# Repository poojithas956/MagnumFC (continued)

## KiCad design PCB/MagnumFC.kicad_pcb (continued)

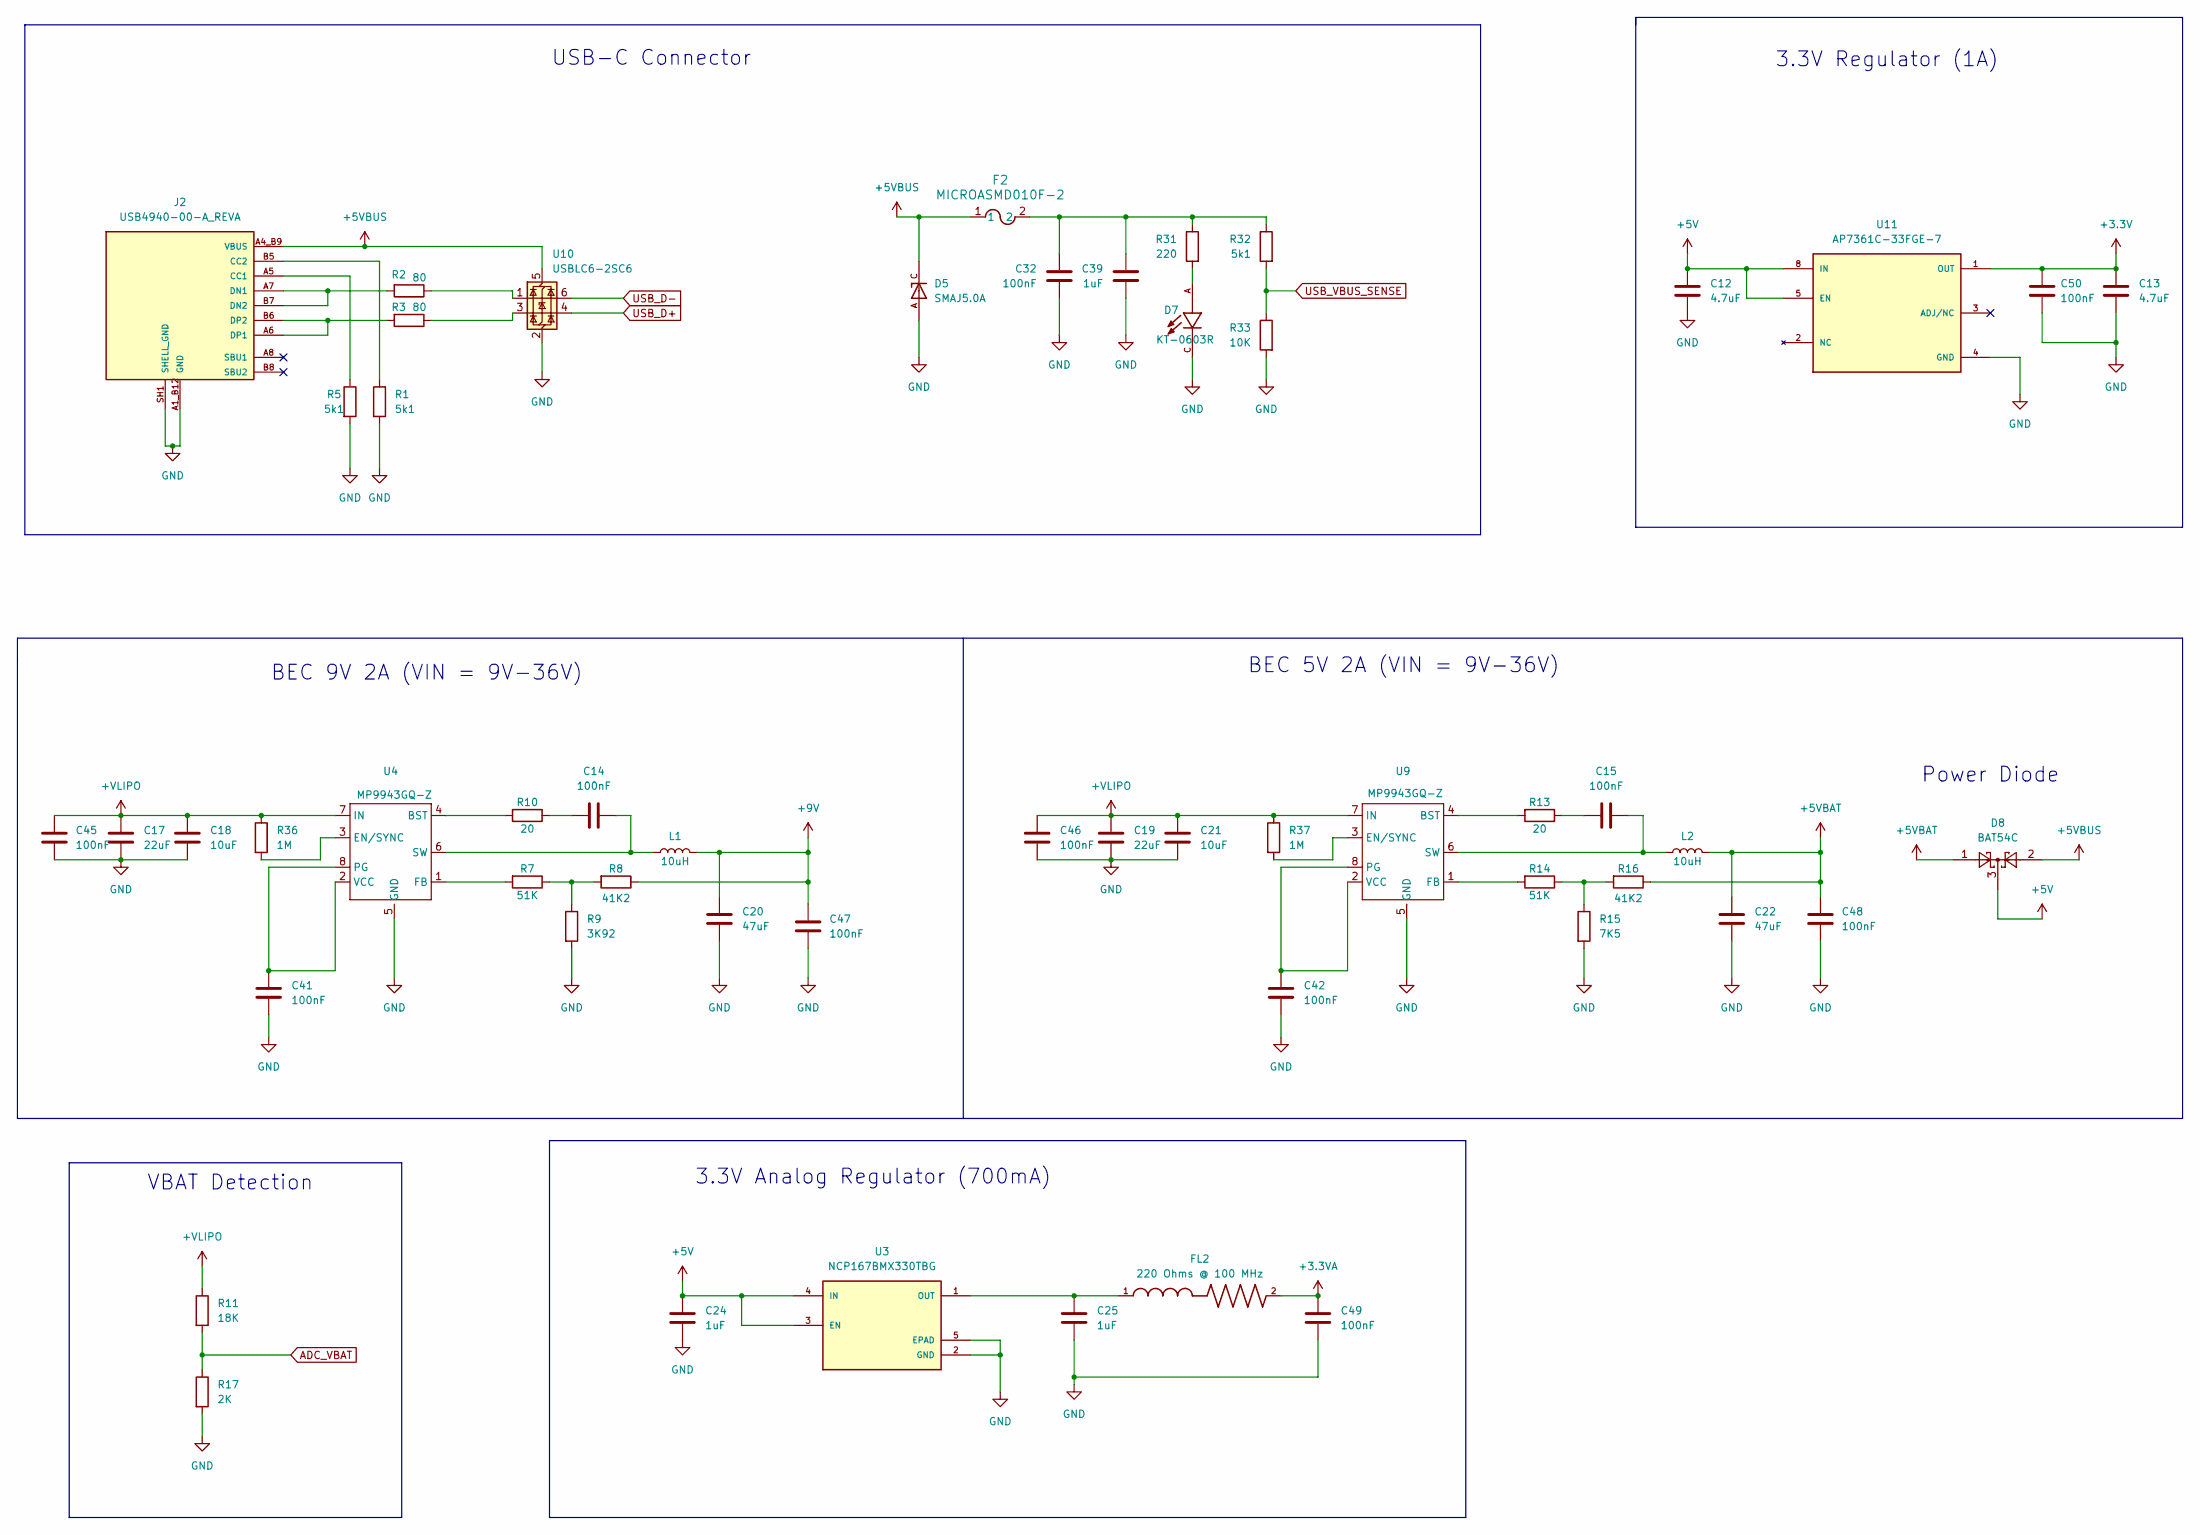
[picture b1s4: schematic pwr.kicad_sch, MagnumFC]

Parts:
C12, C13: 4.7uF; C_0603_1608Metric; MANUFACTURER PART NUMBER CL10A475KO8NNNC; LCSC C19666
C14, C15, C32, C41, C42, C45, C46, C47, C48, C49, C50: 100nF; C_0402_1005Metric; MANUFACTURER PART NUMBER CL05A104KA5NNNC; LCSC C100072
C17, C19: 22uF; C_0805_2012Metric; MANUFACTURER PART NUMBER HGC0805R5226M350NSLJ; LCSC C22367832
C18, C21: 10uF; C_0805_2012Metric; MANUFACTURER PART NUMBER CL21A106KBYQNNE; LCSC C2932476
C20, C22: 47uF; C_0805_2012Metric; MANUFACTURER PART NUMBER CL21A476MPYNNWE; LCSC C5596752
C24, C25, C39: 1uF; C_0402_1005Metric; MANUFACTURER PART NUMBER CL05A105KO5NNNC; LCSC C29266
D5: SMAJ5.0A; DIOM4325X250N; PARTREV S2102; LCSC C83329
D7: KT-0603R; LED_KT-0603R; PARTREV 2013/01/24; LCSC C2286
D8: BAT54C; SOT-23; MANUFACTURER PART NUMBER BAT54CLT1G; LCSC C14308
F2: MICROASMD010F-2; FUSE_MICROASMD010F_LTF; MANUFACTURER PART NUMBER MICROSMD010F-2; LCSC C2649903
FL2: 220 Ohms @ 100 MHz; L_0402_1005Metric; MANUFACTURER PART NUMBER BLM15BB221SN1D; LCSC C85818
J2: USB4940-00-A_REVA; GCT_USB4940-00-A_REVA; PARTREV A; LCSC C54829818
L1, L2: 10uH; L_Changjiang_FTC404020S; MANUFACTURER PART NUMBER GXTC0420-100-MT; LCSC C53198553
R1, R5, R32: 5k1; R_0402_1005Metric; MANUFACTURER PART NUMBER RC0402FR-075K1L; LCSC C105872
R2, R3: 80; R_0402_1005Metric; MANUFACTURER PART NUMBER RC0402FR-0780R6L; LCSC C185392
R7, R14: 51K; R_0402_1005Metric; MANUFACTURER PART NUMBER RC0402FR-0751KL; LCSC C107229
R8, R16: 41K2; R_0402_1005Metric; MANUFACTURER PART NUMBER CRCW040241K2FKED; LCSC C844310
R9: 3K92; R_0402_1005Metric; MANUFACTURER PART NUMBER RC0402FR-073K9L; LCSC C131467
R10, R13: 20; R_0402_1005Metric; MANUFACTURER PART NUMBER RC0402FR-0720RL; LCSC C138031
R11: 18K; R_0402_1005Metric; MANUFACTURER PART NUMBER 0402WGF1802TCE; LCSC C25762
R15: 7K5; R_0402_1005Metric; MANUFACTURER PART NUMBER 0402WGF7501TCE; LCSC C25918
R17: 2K; R_0402_1005Metric; MANUFACTURER PART NUMBER RC0402FR-072KL; LCSC C60488
R31: 220; R_0402_1005Metric; MANUFACTURER PART NUMBER RC0402FR-07220RL; LCSC C112291
R33: 10K; R_0402_1005Metric; MANUFACTURER PART NUMBER RC0402JR-0710KL; LCSC C60489
R36, R37: 1M; R_0402_1005Metric; MANUFACTURER PART NUMBER RC0402JR-071ML; LCSC C93949
U3: NCP167BMX330TBG; VREG_NCP167BMX330TBG; PARTREV 5; LCSC C892227
U4, U9: MP9943GQ-Z; QFN-8_MP9943_MNP; MANUFACTURER PART NUMBER MP9943GQ-Z; LCSC Mouser No: 946-MP9943GQ-Z
U10: USBLC6-2SC6; SOT-23-6; MANUFACTURER PART NUMBER USBLC6-2SC6; LCSC C7519
U11: AP7361C-33FGE-7; SON65P300X300X63-9N; PARTREV 5 - 2; LCSC C151007

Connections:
+3.3V: C13.1, C50.1, U11.1 (OUT); also elsewhere on the board
+3.3VA: C49.1, FL2.2; also elsewhere on the board
+5V: C12.1, C24.1, D8.3, U3.3 (EN), U3.4 (IN), U11.5 (EN), U11.8 (IN); also elsewhere on the board
+5VBAT: C22.1, C48.1, D8.1, L2.2, R16.1
+5VBUS: D5.C, D8.2, F2.1, J2.A4_B9 (VBUS), J2.B4_A9 (VBUS), U10.5 (VBUS)
+9V: C20.1, C47.1, L1.2, R8.1; also elsewhere on the board
+VLIPO: C17.1, C18.1, C19.1, C21.1, C45.1, C46.1, R11.1, R36.1, R37.1, U4.7 (IN), U9.7 (IN); also elsewhere on the board
ADC_VBAT: R11.2, R17.1; also elsewhere on the board
GND: C12.2, C13.2, C17.2, C18.2, C19.2, C20.2, C21.2, C22.2, C24.2, C25.2, C32.2, C39.2, C41.2, C42.2, C45.2, C46.2, C47.2, C48.2, C49.2, C50.2, D5.A, D7.C, J2.A1_B12 (GND), J2.B1_A12 (GND), J2.SH1 (SHELL_GND), J2.SH2 (SHELL_GND), J2.SH3 (SHELL_GND), J2.SH4 (SHELL_GND), R1.2, R5.2, R9.2, R15.2, R17.2, R33.2, U3.2 (GND), U3.5 (EPAD), U4.5 (GND), U9.5 (GND), U10.2 (GND), U11.4 (GND), U11.9 (GND); also elsewhere on the board
unnamed: C14.2, R10.1
unnamed: C15.2, R13.1
unnamed: C32.1, C39.1, F2.2, R31.1, R32.1
unnamed: D7.A, R31.2
unnamed: J2.A5 (CC1), R5.1
unnamed: J2.B5 (CC2), R1.1
unnamed: J2.A7 (DN1), J2.B7 (DN2), R2.2
unnamed: J2.A6 (DP1), J2.B6 (DP2), R3.2
unnamed: R2.1, U10.1 (I/O1)
unnamed: R3.1, U10.3 (I/O2)
unnamed: R7.1, R8.2, R9.1
unnamed: R14.1, R15.1, R16.2
unnamed: C25.1, FL2.1, U3.1 (OUT)
unnamed: R10.2, U4.4 (BST)
unnamed: R36.2, U4.3 (EN/SYNC)
unnamed: R7.2, U4.1 (FB)
unnamed: C41.1, U4.2 (VCC), U4.8 (PG)
unnamed: C14.1, L1.1, U4.6 (SW)
unnamed: R13.2, U9.4 (BST)
unnamed: R37.2, U9.3 (EN/SYNC)
unnamed: R14.2, U9.1 (FB)
unnamed: C42.1, U9.2 (VCC), U9.8 (PG)
unnamed: C15.1, L2.1, U9.6 (SW)
USB_D+: U10.4 (I/O2); also elsewhere on the board
USB_D-: U10.6 (I/O1); also elsewhere on the board
USB_VBUS_SENSE: R32.2, R33.1; also elsewhere on the board

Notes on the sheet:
USB-C Connector
3.3V Analog Regulator (700mA)
VBAT Detection
BEC 5V 2A (VIN = 9V-36V)
BEC 9V 2A (VIN = 9V-36V)
Power Diode
3.3V Regulator (1A)

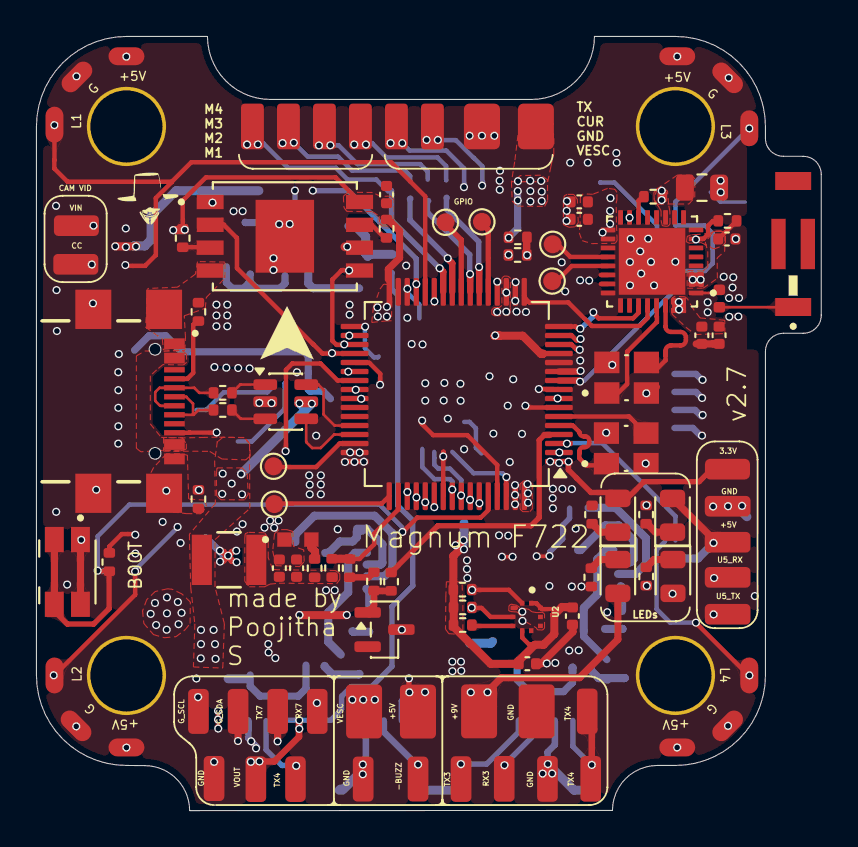
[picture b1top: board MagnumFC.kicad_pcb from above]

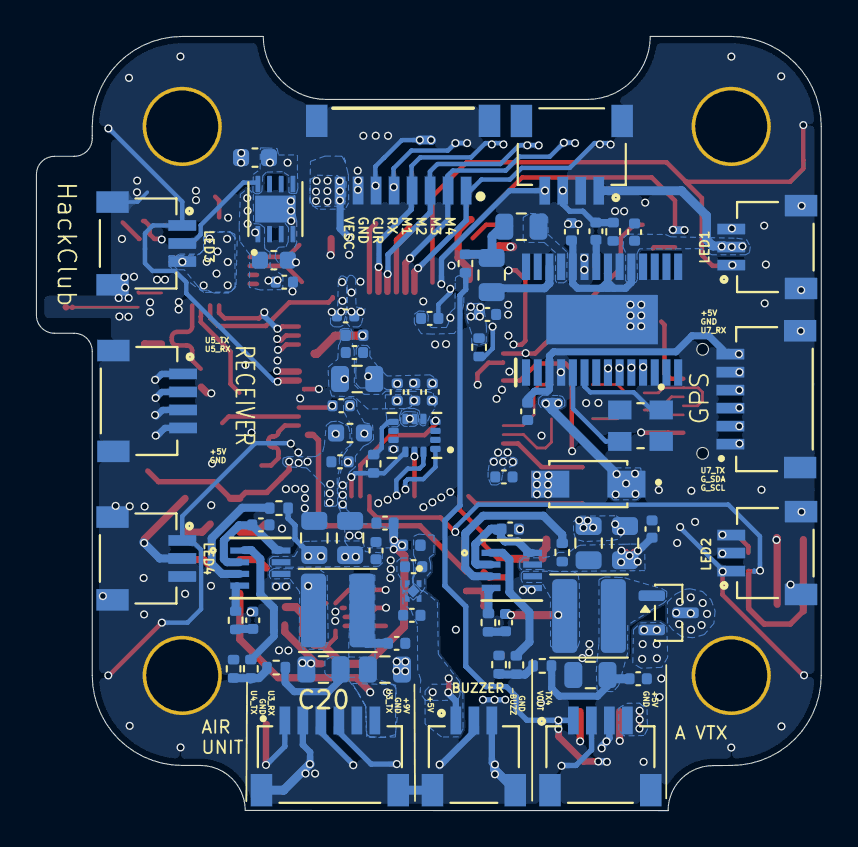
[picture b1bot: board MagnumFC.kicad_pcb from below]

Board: 6 copper layers, 43.6 x 43.0 mm, 180 parts (77 on the bottom side), 107 nets.

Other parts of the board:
TP36#2: TestPoint; TestPoint_Pad_1.0x1.0mm

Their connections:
GND: TP36#2.1 (1_1); also elsewhere on the board

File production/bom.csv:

Designator,Footprint,Quantity,Value,LCSC Part #
"_3, _2, ",,3,,
AT1,ANTENNA_2450AT43B100E,1,2450AT43B100E,C2917721
"C1, C11, C14, C15, C16, C2, C23, C26, C27, C28, C29, C3, C30, C32, C35, C36, C38, C4, C41, C42, C44, C45, C46, C47, C48, C49, C50, C6",0402,28,100nF,C100072
"C10, C33",0402,2,10nF,C15195
"C12, C13, C5",0603,3,4.7uF,C19666
"C17, C19, C31, C40, C43",0805,5,22uF,C22367832
"C18, C21, C37",0805,3,10uF,C2932476
"C20, C22",0805,2,47uF,C5596752
"C24, C25, C34, C39",0402,4,1uF,C29266
C7,0805,1,1uF,C24123
"C8, C9",0402,2,2.2uF,C107369
D1,0805,1,LED2,C2293
D2,0805,1,LED3,C2296
D3,0805,1,LED4,C2297
D4,0805,1,LED1,C2295
D5,DIOM4325X250N,1,SMAJ5.0A,C83329
D7,LED_KT-0603R,1,KT-0603R,C2286
D8,SOT-23,1,BAT54C,C14308
F2,FUSE_MICROASMD010F_LTF,1,MICROASMD010F-2,C2649903
FL1,0402,1,120 Ohms @ 100 MHz,C107331
FL2,0402,1,220 Ohms @ 100 MHz,C85818
IC1,SOP65P640X120-29N,1,AT7456E,C82351
"J1, J9",JST_SM06B-SRSS-TB_LF__SN_,2,SM06B-SRSS-TB_LF__SN_,C2845365
"J10, J13, J14",JST_SM04B-SRSS-TB_LF__SN_,3,SM04B-SRSS-TB_LF__SN_,C2845363
"J12, J3, J5, J7, J8",JST_SM03B-SRSS-TB_LF__SN_,5,SM03B-SRSS-TB_LF__SN_,C2845362
J2,GCT_USB4940-00-A_REVA,1,USB4940-00-A_REVA,C54829818
J6,JST_SM08B-SRSS-TB_LF__SN_,1,SM08B-SRSS-TB_LF__SN_,C160407
"L1, L2",L_Changjiang_FTC404020S,2,10uH,C53198553
L3,0402,1,1.8nH,C77107
Q2,SOT-23,1,AO3400A,C20917
"R1, R32, R5",0402,3,5k1,C105872
"R10, R13",0402,2,20,C138031
R11,0402,1,18K,C25762
"R12, R20, R24, R33, R35, R4, R6",0402,7,10K,C60489
"R14, R7",0402,2,51K,C107229
R15,0402,1,7K5,C25918
"R16, R8",0402,2,41K2,C844310
R17,0402,1,2K,C60488
R18,0402,1,47,C137973
"R2, R3",0402,2,80,C185392
"R21, R31",0402,2,220,C112291
"R22, R34",0402,2,1K,C106235
"R23, R30, R38",0402,3,75,C137841
"R25, R26",0402,2,2.2K,C163447
"R27, R28, R29",0402,3,4.7K,C105871
"R36, R37",0402,2,1M,C93949
R9,0402,1,3K92,C131467
S2,SW_EVQ-P7A01P,1,EVQ-P7A01P,C79167
"TP1, TP10, TP2, TP20, TP21, TP3, TP4, TP40, TP41, TP42, TP43, TP44, TP45, TP46, TP47, TP48, TP49, TP5, TP50, TP51, TP6, TP7, TP8, TP9",TestPoint_Pad_D1.0mm,24,TestPoint,-
"TP11, TP12",TestPoint_Pad_D2.0mm,2,TestPoint,-
"TP13, TP14, TP15, TP16, TP18, TP19, TP23, TP24, TP25, TP26, TP27, TP28, TP29, TP30, TP32, TP33, TP34, TP35, TP36_2, TP38, TP39",TestPoint_Pad_1.0x1.0mm,21,TestPoint,-
"TP17, TP31, TP37",TestPoint_Pad_2.0x2.0mm,3,TestPoint,-
TP36,TestPoint_Pad_1.0x1.0mm,1,TestPoint,
U1,LQFP-64_10x10mm_P0.5mm,1,STM32F722RETx,C118207
U10,SOT-23-6,1,USBLC6-2SC6,C7519
U11,SON65P300X300X63-9N,1,AP7361C-33FGE-7,C151007
U2,XDCR_BMP388,1,BMP388,C779278
U3,VREG_NCP167BMX330TBG,1,NCP167BMX330TBG,C892227
"U4, U9",QFN-8_MP9943_MNP,2,MP9943GQ-Z,Mouser No: 946-MP9943GQ-Z 
U5,QFN50P500X500X90-33N,1,ESP32-C3,C2838500
U6,PQFN50P300X250X97-14N,1,ICM-42688-P,"C1850418,  Mouser No: 410-ICM-42688-P "
U7,IC_W25N04KVZEIR,1,W25Q256JVEIQ,C97522
Y1,XTAL_ABM8-27.000MHZ-B2-T,1,ABM8-27.000MHZ-B2-T,C1985251
Y2,XTAL_C3E-40.000-10-1015-X-R,1,C3E-40.000-10-1015-X-R,C5444549
Y3,XTAL_C3E-8.000-18-3030-X-R,1,C3E-8.000-18-3030-X-R,C2682775

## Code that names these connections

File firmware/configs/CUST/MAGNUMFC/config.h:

/*
 * MagnumFC Betaflight target draft
 *
 * This configuration is an unvalidated starting point for Betaflight 4.5+.
 * It intentionally does not define motor outputs or onboard flash because
 * the board design has unresolved issues documented in firmware/README.md.
 * Do not use this as flight-ready firmware.
 */
#pragma once

#define FC_TARGET_MCU STM32F722
#define BOARD_NAME MAGNUMFC
#define MANUFACTURER_ID CUST
#define SYSTEM_HSE_MHZ 27

#define USE_GYRO
#define USE_ACC
#define USE_GYRO_SPI_ICM42688P
#define USE_ACC_SPI_ICM42688P
#define SPI3_SCK_PIN PB3
#define SPI3_SDI_PIN PB4
#define SPI3_SDO_PIN PB5
#define GYRO_1_SPI_INSTANCE SPI3
#define GYRO_1_CS_PIN PB9
#define GYRO_1_EXTI_PIN PB8
#define GYRO_1_ALIGN CW0_DEG /* Must be confirmed by checking board orientation. */

#define USE_BARO
#define USE_BARO_BMP388
#define I2C1_SCL_PIN PB6
#define I2C1_SDA_PIN PB7
#define BARO_I2C_INSTANCE I2CDEV_1

#define USE_MAX7456
#define SPI2_SCK_PIN PB13
#define SPI2_SDI_PIN PB14
#define SPI2_SDO_PIN PB15
#define MAX7456_SPI_INSTANCE SPI2
#define MAX7456_SPI_CS_PIN PB2

/* UART numbers below follow the STM32 alternate-function pin pairs, not the
 * net labels in the schematic. The exposed connector assignments need review. */
#define UART1_TX_PIN PA9
#define UART1_RX_PIN PA10
#define UART2_TX_PIN PA2
#define UART2_RX_PIN PA3
#define UART4_TX_PIN PA0
#define UART4_RX_PIN PA1
#define UART5_TX_PIN PC12
#define UART5_RX_PIN PD2
#define UART6_TX_PIN PC6
#define UART6_RX_PIN PC7

#define ADC_VBAT_PIN PC0
#define ADC_CURR_PIN PA4
